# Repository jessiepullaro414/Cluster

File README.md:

# Cluster

**How to run everything: [RUNNING.md](RUNNING.md).**

Digital restomod instrument cluster for a 1966 Mustang: round displays in the stock round holes, custom reprinted faceplate, stock outer dash opening (457.2 x 116.69mm hard limit, 441.09 x 105.54mm inner).

The center gauge runs Linux with LIVI (CarPlay / Android Auto) or Android Automotive; the four small gauges are driven by a separate MCU board. The boards share a CAN bus with `ecu-pcb`.

## Boards

| Dir | Role | Core | Board |
|---|---|---|---|
| [brain/](brain/) | Centre-screen board, **the same in every car**: wireless Android Auto / CarPlay host with sound, two screen ports | Toradex Verdin iMX95 WB SoM (screwed down on M2 standoffs, heatsink-ready), screen port A (MIPI DSI) and B (LVDS, single or dual link), TAC5112-Q1 audio codec, two USB-C host ports | 127.5 x 95.3mm |
| [panel-tsd/](panel-tsd/) | Panel board for the TSD TST040HDBC-42 4 in 800-nit round MIPI panel: its FPC connector, +/-6 V bias, backlight, and the input from port A | TPS65131-Q1, TPS61165-Q1 | 75.4 x 52.3mm |
| [gauges/](gauges/) | 4 small aux gauges, resistive sender front end, Hall or two-wire VR speed, tach and six 12 V indicator-lamp inputs | NXP S32K144, 4x GC9A01 round SPI | 447.1 x 61.0mm |

**One brain board for every car (2026-10-20).** The centre-screen board no longer depends on the car or the panel. Everything that does moved off it: the panel's connector, bias supply, polarity jumpers and backlight are on a small board behind that panel, joined to the brain board by a ribbon on one of two screen ports (DSI for MIPI panels, LVDS for automotive and large panels; an RGB panel gets an LVDS-to-RGB receiver on its panel board). Each port has its own current-limited 5 V switch, panel control lines, an I2C bus and a panel-ID resistor the software reads. Pin tables and the rules for a new panel board: [docs/screen-ports.md](docs/screen-ports.md). A different car (a 1968 Mustang, a 1972 Alfa Romeo GTV) needs its own gauges board (generated from the same scripts with its own gauge positions), panel boards for its screens and a faceplate; the brain board stays the same. The 1966-only `display/` and the RGB variant `display-rgb/` are in `archive/`; the RGB panel's own panel board waits for that panel's datasheet. Not confirmed yet: that the Verdin iMX95 drives the DSI and LVDS screens independently at the same time (the i.MX 95 can; question 9 in `docs/rfq-drafts.md` section 2).

**Status: prototype, not yet ordered.** Fabrication readiness board by board: `docs/electrical-review.md` section 9.4 (panel-tsd/ should wait for TSD's connector answer); first power-up checklist: section 9.5. All three boards are six-layer and routed with 0 unconnected nets, and have generated BOMs (`brain/ClusterBrain_BOM.html`, `panel-tsd/ClusterPanelTSD_BOM.html`, `gauges/ClusterGauges_BOM.html`). brain/ and panel-tsd/ are ERC-clean (0 violations); gauges/ shows 4 known ERC items (a SWCLK pin, the MCU and buck supply pins flagged as undriven, and a `+5V` power-flag note). DRC: brain/ reports 4 `hole_clearance` errors (the USB-C receptacle J17's own land pattern: its GND pads sit 0.194 mm from its locating pegs against the 0.25 mm default, see `fab/README.md`) plus silkscreen and library-copy warnings; panel-tsd/ reports only `solder_mask_bridge` errors at the intentional open polarity jumpers JP1/JP2; gauges/ the same at its open CAN-termination jumpers JP1/JP2, plus warnings. Nothing has been fabricated, powered or firmware-tested. Mechanical fit is checked against a 3D assembly in a factory-style housing (`docs/dash-assembly.md`, no clashes), and gauges/ (447.1 mm) is wider than the 441.09 mm inner opening dimension, within the 457.2 mm outer limit. Installing in a car with the stock wiring (grounds, the ammeter wires, the dimmer, warning lamps, CAN termination): `docs/harness.md`.

**The owner's decisions, 2026-11-04** (`docs/electrical-review.md` 9.3): two-wire VR speed sensors are supported directly (J12, U13, simulated only so far); the ALT gauge is a voltmeter; an unsuppressed load dump may sacrifice the TVS and fuse; friction-lock harness headers stay as they are; a parked module whose wake timer cannot be set powers off rather than sleeps. The dash-light knob is read by a pulsed load on the board, so nothing goes under the dash (simulated only so far; the rheostat's 12 ohm full scale is an estimate until a real switch is measured).

**Product review for fabrication, 2026-11-03** (`docs/electrical-review.md` section 9): both 12 V input stages rewired to TI's LM74930 topology (the sense resistor had been on the input side, which broke the short-circuit protection, put 12 V across a +-0.3 V pin pair at every power-up and let a reversed battery reach pins rated -1 V), with an inrush (dV/dt) network, a bidirectional TVS so a reversed battery is simply blocked, and Kelvin sense taps built into the resistor's land pattern (the router's copper had been pulling the gauges breaker from 1.49 A down to about 0.45 A). brain/ gained an ignition power latch: the key starts the module from any state and software can switch the board fully off with the car parked. gauges/ measures each sender with its excitation on and off, cancelling the engine-to-dash ground offset that made a hot engine or a full tank read as a shorted sender; the sender excitation and the 12 V pull-up rail (now also the Hall sender's supply on J9 pin 3) switch off with the car off; the car-CAN terminator is switched in with solder jumpers. Open decisions are in section 9.3.

**Product review, 2026-10-18** (`docs/electrical-review.md` section 8a): the Verdin module now has Toradex's four M2 standoffs (S1/S2 hold-down, S3/S4 for the Verdin Industrial Heatsink) and a keepout that follows the real module outline; the LM74930 FETs on both boards are Vishay SQJ460AEP (PowerPAK SO-8L) instead of the NRND SOT-23 PMV55ENEA; the gauges buck has the datasheet's 2.2 uH / 16 V output parts; the line-out ESD array is bidirectional; the panel-bias outputs use 16 V capacitors; the inner small gauges moved to the measured +/-118 mm. Still open before ordering: the TSD panel's pinout and connector (`docs/rfq-drafts.md` section 1), the Verdin module's availability and heatsink (section 2), the depth stack-up (`docs/mechanical-stackup.md`), the backlight driver's temperature (D-04), the small displays' -20 to +70 C rating (G-15, section 6), and licensing.

## How the boards talk

gauges/ is the gateway. It is the only board that touches the car CAN bus (CAN0, receive-only in firmware) and it forwards filtered values to brain/ over a private two-node CAN link (gauges/ CAN1 to brain/ CAN). Android therefore cannot transmit on the vehicle bus. The protocol (`protocol/can_protocol.py`, revision 2) generates the DBC, a spec and a C header; the private link carries a rolling counter and CRC-8, and the car-bus side has a selectable Haltech V2 profile. Speed comes from a Hall-effect sender on gauges/ (for cable-driven cars) or from the ECU over CAN. gauges/ also reads six 12 V-active indicator lamps (left/right turn, high beam, brake, alternator, oil; each has a DNP pull-up for a ground-switched lamp). The two turn-signal arrows on the dash are physical: green LEDs (ROHM CSL0902ET1C) on gauges/, each lit straight from its turn-signal wire through a 1.8 k resistor so they flash like the old bulbs even with the software off (their X positions are placeholders until the faceplate drawing exists) and a tach input (ECU or coil-driver output; coil-negative on a points ignition is not validated), sent to brain/ in the `Indicators` message (which also carries the dimmer level) and the `Rpm` signal. brain/ has a rotary-dial input (J11), an ignition wake circuit, an audio path (balanced stereo line-out J14 and a microphone J15 on a TI TAC5112-Q1 codec), a USB-C host port (J17, 1.5 A, for a phone or a wireless-projection dongle), a DNP 1x6 header (J16) for an Apple MFi coprocessor daughterboard, with I2C, reset and a GPIO-switched 5 V supply and bench headers for the A55 console UART (J12), USB (J13), JTAG (J8) and buttons (J9).

## Known limits of the layouts

- **Six layers, two solid GND planes (2026-10-19).** Stack-up JLC06161H-3313: F.Cu signal, In1 GND, In2 signal, In3 signal plus the +5V (brain/, panel-tsd/) or +3V3 (gauges/) pour, In4 GND, B.Cu signal. Every net except GND gets a net-class layer restriction in the router input (`use_layer F.Cu In2.Cu In3.Cu B.Cu`; FreeRouting ignores a layer_rule "active off"), so In1 and In4 carry no track at all, only the GND fill and vias, and `review/layout_checks.py` fails a board if any other net lands there. Every outer-layer signal has a GND plane 0.0994 mm below it. In2 and In3 sit 0.55 mm from their planes and only 0.11 mm from each other, so a signal on one can couple broadside into the other. On brain/ the USB-C phone pair (USB2_DP/DN, about 30 mm) runs about 25 mm on In3, both legs together. PG_5V, the buck's own power-good pin, runs on F.Cu 0.24 mm from its switch copper beside U2 (`layout_checks.py`). On panel-tsd/ the backlight PWM line crosses the backlight's switch node in plan view on In3, with the In1 plane between them. Until 2026-10-19 both boards were four-layer with signals routed through the GND and supply pours (about 1.5 m on the old display/, 9 m on gauges/). gauges/ routes VIN_PROT, VIN_FUSED and +5V at 0.4 mm from the start, and every power net on it now passes `layout_checks.py`'s 20 K current check. Details: `docs/electrical-review.md` section 8b.
- **Battery-path and port copper on brain/ (2026-10-20, from display/).** VBAT_IN, VBAT_F, SENSE_OUT, COMMON and +12V_PROT (up to 2.6 A behind the 5 A fuse) now route on the 1 oz outer layers only, at 0.3 mm with 1.0/0.5 mm vias, and after widening each gets an F.Cu pour in a 2 mm band around its own copper (`route_board.py`, `BATTERY_PATH_NETS` and `add_battery_pours()`). No battery copper is on In2/In3 any more (until now about 60 mm of VBAT_F was, which IPC-2221 rates at about 1.3 A). `review/layout_checks.py` now rates each of these nets along the path the current takes (J2 -> F1 -> R1 -> Q2 -> Q1 -> the buck's VIN pins), counting the pour beside a track and the vias, and lists branch copper to milliamp pins (LM74930 sense pins, small caps) separately. R2 and C3 sit on R1's input side (`brain/cells.py`), so nothing lies between R1 and Q2. Each screen port's switched 5 V (PORTA_5V, PORTB_5V, up to the switch's 1.98 A) gets the same outer-layer route and pour. VBAT_IN, VBAT_F, SENSE_OUT and PORTA_5V pass; what is left are short necks where the path meets a pin: COMMON 2.1 mm at down to 0.34 mm at the FETs' source pins, +12V_PROT 1.0 mm at down to 0.56 mm at the buck's 0.4 mm VIN pins, PORTB_5V 0.7 mm at 0.45 mm, each a few mW at full current. Still worth a thermal-camera look at 2.5 A on the first board. Details: `docs/electrical-review.md` section 8b.
- **brain/ shrunk (2026-11-06).** 184.8 x 104.9 mm to 127.5 x 95.3 mm, 37 % less area, parts' courtyards from 33 % to 52 % of the board. The battery path and the screen ports' 5 V are planned copper now as well, worst 15 K by IPC-2221, and J2 sits on the right edge with its wire mouth facing out: it used to face the Verdin module. Each USB-C pair has a common-mode choke. `docs/electrical-review.md` section 9.5c. gauges/ J1 had the same mouth fault: see below.
- **gauges/ J1 (2026-11-06).** Its wire mouth looked down the board at C59. It's turned round now and sits at the top edge, with the fuse beside pin 1 and the input TVS beside the fuse, and the board is 61.0 mm tall, from 65.9. The screen connectors didn't move. J1's wires are in the housing's clash check with 0.5 mm to spare, on assumed wire and bend sizes, and no way out of the housing is drawn for them yet. Calculated, not measured. `docs/electrical-review.md` section 9.5d.
- **5 V copper on brain/ (2026-11-06).** Until now all of the buck's output left L1 on one 0.2 mm track: 1021 K by IPC-2221 at the Alfa's 5.7 A, 284 mV down at J1, and `layout_checks.py` passed it as "pour-carried?". `brain/power_route.py` now plans the copper that carries current, with vias into the In3 pour at L1, J1 and each port switch, and `review/power_sheet.py` solves the net with its pours as copper sheets for both cars: worst track 2.7 K, worst via 4.3 K, 13 mV. It gates each route and the fab package. Calculated, not measured. The same re-route left no under-width copper on the battery path or the ports, so the necks listed above are gone. Details: `docs/electrical-review.md` section 9.5b.
- **Screen-port pairs.** On brain/ every DSI and LVDS pair runs from the Verdin socket straight to its port connector on F.Cu over the In1 plane, planned by `brain/fan_route.py` (no length difference inside a pair; DSI about 5.4 mm, LVDS about 35 mm, under the module), with GND guard tracks between pairs where the socket has a ground pin. On panel-tsd/ the three DSI lanes and the clock are autorouted on F.Cu and B.Cu only (each leg is about 52 ohm on its own, so a pair stays near 100 ohm even where the router separates its legs); the router's skew inside a pair is up to 5.5 mm (about 37 ps, 2 % of a bit at 500 Mbit/s). The 0.16 mm geometry is field-solved by `review/dsi_impedance.py` (96.4 to 103.1 ohm differential on JLC06161H-3313); that is a 2-D solve on the board house's nominal stack-up, not a measurement: order with controlled impedance and a coupon (`fab/README.md`).
- The panel connector, the panel bias-pin polarity (open jumpers JP1/JP2; a diode-test check before bridging is in `fab/README.md`) and the wake-pin polarity are unconfirmed. The panel bias rails are set to +5.98 V and -6.05 V, inside the ICNL9707 driver's 4.5 to 6.5 V operating range with margin to its 6.6 V absolute maximum (the panel sheet's 6.5 V is at the top of that range; question 8 in `docs/rfq-drafts.md`).

Open items and rationale live in the working plan, not here. Panel: TSD TST040HDBC-42 (4in round, 800 nits, -30..+80C, 101.52 mm active circle: fits the 105.54 mm dash opening height, but NOT a stock 89.26 mm speedometer hole without cropping, see `docs/mechanical-fit.md`). Harness connectors are decided for both boards (`docs/harness.md`, 2026-10-17). Known TBDs: the panel's unresolved bias-pin polarity (open solder jumpers JP1/JP2), measured sender curves (`docs/sender-calibration.md`: the dash shows the raw sender resistance for this), and everything that needs real hardware. The gauges firmware's key-off sleep (S32K144 VLPS, woken by the ignition line) is written and host-tested, not run on a board.

## Wireless Android Auto / CarPlay hardware (2026-10-16)

Required by the owner. brain/ carries the physical pieces: audio codec and connectors, two USB-C host ports, the Verdin WB module's Wi-Fi 6 / Bluetooth 5.4 (antennas are a mechanical item) and a reserved DNP MFi access point. **Licensing (Apple MFi for CarPlay, Google's Android Auto receiver terms) is a separate business gate (plan item B5) that hardware does not solve.** Wiring, antenna rules, software bring-up and what is unverified: [docs/audio-and-usb.md](docs/audio-and-usb.md).

## Workflow

Everything is generated from scripts. Never hand-edit the KiCad files; change the script and regenerate. In `brain/`, `panel-tsd/` or `gauges/`:

```
python build_schematic.py   # schematic + ERC self-checks
python build_pcb.py         # placement + DRC-style self-checks
python route_board.py       # FreeRouting (brain/ also adds the planned screen-port pairs), verified against real kicad-cli DRC
python ../review/layout_checks.py <dir>   # GND planes clean, switch-node spacing, fast-net layers, power-path current
python ../run_drc.py <Board>.kicad_pcb
python build_bom.py         # BOM with coverage/value-spelling checks
```

`route_board.py` needs `tools/freerouting-2.2.4.jar` (gitignored, ~57MB; download from the FreeRouting releases) and a JRE.

## Archive

[archive/](archive/) holds superseded work kept for reference only, not maintained:

- `display-1966/`: the 1966 Mustang's one-panel Verdin carrier (2026-09-25 to 2026-10-20), replaced by brain/ + panel-tsd/; its fab package is in `display-1966/fab/`.
- `display-rgb/`: display/ with an LVDS-to-RGB receiver for the Anders 4.2 in RGB panel, routed; the receiver becomes that panel's panel board once its datasheet arrives.
- `single-board-s32k144-bt817aq/`: the original one-board design (S32K144 + BT817AQ + round ST7701S speedo + 4 GC9A01), fully routed 252/252 before the Android pivot.
- `.../sense-abandoned-bar-panel-attempt/`: an unfinished CAN-only sensor board from the abandoned wide bar-panel direction.

Scripts there use their old relative paths (`tools/`, `run_drc.py`) and will need adjusting to run.

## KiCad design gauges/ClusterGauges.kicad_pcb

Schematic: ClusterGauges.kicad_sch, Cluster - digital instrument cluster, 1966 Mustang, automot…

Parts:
C1: 10uF 50V X7R CIN (AEC-Q200); C_1210_3225Metric
C2, C45: 22uF 16V X7R COUT (AEC-Q200); C_1210_3225Metric
C3: 1uF X7R (AEC-Q200); C_0603_1608Metric
C4, C5: 18pF (AEC-Q200); C_0603_1608Metric
C6, C7: 100nF (AEC-Q200); C_0603_1608Metric
C8: 1uF (AEC-Q200); C_0603_1608Metric
C11: 100nF BOOT cap (AEC-Q200); C_0603_1608Metric
C12: 1uF VCC decouple (AEC-Q200); C_0603_1608Metric
C13, C40: 100nF VCC decouple (AEC-Q200); C_0603_1608Metric
C14, C41: 100nF VIO decouple (AEC-Q200); C_0603_1608Metric
C15: 100nF VBAT decouple (AEC-Q200); C_0603_1608Metric
C16, C42: 4.7nF SPLIT stabilization (AEC-Q200); C_0603_1608Metric
C17, C18, C19, C20: 100nF VCI decouple (AEC-Q200); C_0603_1608Metric
C28: 100nF ADC_FUEL smoothing (AEC-Q200); C_0603_1608Metric
C29: 100nF ADC_OIL smoothing (AEC-Q200); C_0603_1608Metric
C30: 100nF ADC_TEMP smoothing (AEC-Q200); C_0603_1608Metric
C31: 100nF ADC_BATT smoothing (AEC-Q200); C_0603_1608Metric
C43: 1nF input filter (AEC-Q200); C_0603_1608Metric
C44: 10nF input filter (AEC-Q200); C_0603_1608Metric
C46: 220nF 50V CHF at VIN (AEC-Q200); C_0603_1608Metric
C47: 1uF CVS (50V); C_0805_2012Metric
C48: 100nF CCAP (50V); C_0603_1608Metric
C49: 100nF CTMR; C_0603_1608Metric
C50: 10nF input filter, Left turn (AEC-Q200); C_0603_1608Metric
C51: 10nF input filter, Right turn (AEC-Q200); C_0603_1608Metric
C52: 10nF input filter, High beam (AEC-Q200); C_0603_1608Metric
C53: 10nF input filter, Brake / parking brake (AEC-Q20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; C_0603_1608Metric
C54: 10nF input filter, Alternator / charge (AEC-Q200); C_0603_1608Metric
C55: 10nF input filter, Oil pressure (AEC-Q200); C_0603_1608Metric
C56: 10nF input filter, tach (AEC-Q200); C_0603_1608Metric
C57: 220nF input filter, dash dimmer (AEC-Q200); C_0603_1608Metric
C58: 1uF X7R LDO input (AEC-Q200); C_0603_1608Metric
C59, C60: 10uF 50V X7S extra bulk at VIN_PROT (AEC-Q200); C_1210_3225Metric
C61: 4.7nF 50V CdVdT, HGATE inrush limit (AEC-Q200); C_0603_1608Metric
C62: 100nF 50V CIN at the fused input (AEC-Q200); C_0603_1608Metric
C63: 100nF 50V U12 VS decoupling (AEC-Q200); C_0603_1608Metric
C64: 10nF 50V VPULL output (ESD, AEC-Q200); C_0603_1608Metric
C65: 1uF X7R U11 input (AEC-Q200); C_0603_1608Metric
C66: 100nF SENDER_EXC (AEC-Q200); C_0603_1608Metric
C67: 100nF SENDER_BIAS (AEC-Q200); C_0603_1608Metric
C68: 4.7nF VR filter, wire A (AEC-Q200); C_0603_1608Metric
C69: 4.7nF VR filter, wire B (AEC-Q200); C_0603_1608Metric
C70: 100nF U13 supply (AEC-Q200); C_0603_1608Metric
D1: SMCJ33CA bidirectional automotive TVS (AEC-Q101) 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; D_SMC
D10, D11: BAV99-Q input clamp (AEC-Q101); SOT-23
D12: BAV99-Q fuel input clamp (AEC-Q101); SOT-23
D13: BAV99-Q oil input clamp (AEC-Q101); SOT-23
D14: BAV99-Q temp input clamp (AEC-Q101); SOT-23
D15: BAV99-Q battery divider clamp (AEC-Q101); SOT-23
D16: BAV99-Q input clamp, Left turn (AEC-Q101); SOT-23
D17: BAV99-Q input clamp, Right turn (AEC-Q101); SOT-23
D18: BAV99-Q input clamp, High beam (AEC-Q101); SOT-23
D19: BAV99-Q input clamp, Brake / parking brake (AEC-Q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; SOT-23
D20: BAV99-Q input clamp, Alternator / charge (AEC-Q10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; SOT-23
D21: BAV99-Q input clamp, Oil pressure (AEC-Q101); SOT-23
D22: BAV99-Q input clamp, tach (AEC-Q101); SOT-23
D23: BAV99-Q input clamp, dash dimmer (AEC-Q101); SOT-23
D24: BAV99-Q reverse clamp, Left turn arrow LED (AEC-Q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; SOT-23
D25: BAV99-Q reverse clamp, Right turn arrow LED (AEC-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; SOT-23
D26: CSL0902ET1C green LED, Left turn arrow; CSL0902_1608
D27: CSL0902ET1C green LED, Right turn arrow; CSL0902_1608
D28: SM24CANB-02HTG TVS on the car CAN bus, at J7 (AEC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; SOT-23
D29: SM24CANB-02HTG TVS on the fuel and oil sender wir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; SOT-23
D30: SM24CANB-02HTG TVS on the coolant sender wire, at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; SOT-23
D31: SM24CANB-02HTG TVS on the private CAN link, at J8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; SOT-23
D32: SM24CANB-02HTG TVS on the Hall speed wire, at J9 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; SOT-23
D33: SZMMSZ3V6T1G 3.6V zener clamp on +3V3, absorbs a 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; D_SOD-123
D34: BAV99-Q LM74930 VS supply diode, blocks a reverse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; SOT-23
D35: BAV99-Q input clamp, VR wire A (AEC-Q101); SOT-23
D36: BAV99-Q input clamp, VR wire B (AEC-Q101); SOT-23
D37: BAV99-Q both sections in series, blocks a negativ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; SOT-23
F1: Mini blade holder, 2A Littelfuse 297 fuse (SAE J2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; Fuseholder_Blade_Mini_Keystone_3568
J1: Phoenix MKDS 1,5/3-5,08: 12V, GND, ignition (20 A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; TerminalBlock_Phoenix_MKDS-1,5-3-5.08_1x03_P5.08mm_Horizont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
J2: SWD Tag-Connect TC2030-IDC-NL (pin order per Tag-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; Tag-Connect_TC2030-IDC-NL_2x03_P1.27mm_Vertical
J7: KK-254 22-27-2051: CAN0 + 3 sender inputs (22 AWG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; Molex_KK-254_AE-6410-05A_1x05_P2.54mm_Vertical
J8: KK-254 22-27-2031, private CAN link to display/ J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; Molex_KK-254_AE-6410-03A_1x03_P2.54mm_Vertical
J9: KK-254 22-27-2031, Hall speed sender (signal, gro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; Molex_KK-254_AE-6410-03A_1x03_P2.54mm_Vertical
J10: KK-254 22-27-2081, indicator lamp inputs (6 x 12 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; Molex_KK-254_AE-6410-08A_1x08_P2.54mm_Vertical
J11: KK-254 22-27-2021, tach input (signal + ground; 2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; Molex_KK-254_AE-6410-02A_1x02_P2.54mm_Vertical
J12: KK-254 22-27-2021, two-wire VR speed sensor (22 A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; Molex_KK-254_AE-6410-02A_1x02_P2.54mm_Vertical
JP1: Solder jumper: bridge with JP2 to terminate the c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; SolderJumper-2_P1.3mm_Open_RoundedPad1.0x1.5mm
JP2: Solder jumper: bridge with JP1 to terminate the c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; SolderJumper-2_P1.3mm_Open_RoundedPad1.0x1.5mm
L1: 2.2uH power XAL5030-222ME (AEC-Q200); L_Coilcraft_XAL5030-XXX
L2: ferrite bead (AEC-Q200); L_0603_1608Metric
Q1: SQJ460AEP ideal diode (DGATE); PowerPAK_SO-8L_Single
Q2: PMV37ENEA automotive (AEC-Q101) - shared aux-gaug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; SOT-23
Q3: SQJ460AEP pass (HGATE); PowerPAK_SO-8L_Single
Q4: MMBT5551Q dimmer test load switch (AEC-Q101); SOT-23
R1: 10k pull-up (AEC-Q200); R_0603_1608Metric
R2: 10k (AEC-Q200); R_0603_1608Metric
R3: 2.49k (AEC-Q200); R_0603_1608Metric
R4, R5: 60R split termination (AEC-Q200), switched in by 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; R_0603_1608Metric
R6, R7, R8, R9: 120R VLED series (self-calculated for ~15mA at 5V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; R_0603_1608Metric
R10: 100R BL_EN gate resistor (AEC-Q200); R_0603_1608Metric
R11: 10k LPSPI2_SIN pull-down, idle-state definition (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; R_0603_1608Metric
R16: 1k fuel pull-up to SENDER_EXC, 1206: a wire short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; R_1206_3216Metric
R17: 1k oil pull-up to SENDER_EXC, 1206 (AEC-Q200); R_1206_3216Metric
R18: 1k coolant temp pull-up to SENDER_EXC, 1206 (AEC-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; R_1206_3216Metric
R19: 49.9k battery divider top, self-calculated for 9-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; R_0603_1608Metric
R20: 10k battery divider bottom, self-calculated for 9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; R_0603_1608Metric
R40: 10k STB pulldown, normal mode while MCU resets (A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; R_0603_1608Metric
R41, R42: 60R split termination (AEC-Q200); R_0603_1608Metric
R43: 4.7k pull-up to VPULL for open-collector senders 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; R_0603_1608Metric
R44: 33k series (AEC-Q200); R_0603_1608Metric
R45: 15k divider bottom (AEC-Q200); R_0603_1608Metric
R46: 56k series (AEC-Q200); R_0603_1608Metric
R47: 27k divider bottom (AEC-Q200); R_0603_1608Metric
R48: 49.9R 1% RSET; R_0603_1608Metric
R49: 5m 1% sense (Susumu KRL3216E-M-R005-F-T5); R_1206_3216Metric_Kelvin
R50: 80.6k 1% RILIM (1.5A breaker); R_0603_1608Metric
R51: 100k OV top; R_0603_1608Metric
R52: 2.05k OV bot (clamp 29.9V); R_0603_1608Metric
R53: 100k UV top; R_0603_1608Metric
R54: 11.5k UV bot (cut-off 5.5V); R_0603_1608Metric
R55: 1k fuel ADC series (AEC-Q200); R_0603_1608Metric
R56: 1k oil ADC series (AEC-Q200); R_0603_1608Metric
R57: 1k temp ADC series (AEC-Q200); R_0603_1608Metric
R58: 33k series, Left turn (AEC-Q200); R_0603_1608Metric
R59: 15k divider bottom, Left turn (AEC-Q200); R_0603_1608Metric
R60: 4.7k pull-up to VPULL, DNP: fit only if the Left 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; R_0603_1608Metric
R61: 33k series, Right turn (AEC-Q200); R_0603_1608Metric
R62: 15k divider bottom, Right turn (AEC-Q200); R_0603_1608Metric
R63: 4.7k pull-up to VPULL, DNP: fit only if the Right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; R_0603_1608Metric
R64: 33k series, High beam (AEC-Q200); R_0603_1608Metric
R65: 15k divider bottom, High beam (AEC-Q200); R_0603_1608Metric
R66: 4.7k pull-up to VPULL, DNP: fit only if the High 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; R_0603_1608Metric
R67: 33k series, Brake / parking brake (AEC-Q200); R_0603_1608Metric
R68: 15k divider bottom, Brake / parking brake (AEC-Q2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; R_0603_1608Metric
R69: 4.7k pull-up to VPULL, DNP: fit only if the Brake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; R_0603_1608Metric
R70: 33k series, Alternator / charge (AEC-Q200); R_0603_1608Metric
R71: 15k divider bottom, Alternator / charge (AEC-Q200); R_0603_1608Metric
R72: 4.7k pull-up to VPULL, DNP: fit only if the Alter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; R_0603_1608Metric
R73: 33k series, Oil pressure (AEC-Q200); R_0603_1608Metric
R74: 15k divider bottom, Oil pressure (AEC-Q200); R_0603_1608Metric
R75: 4.7k pull-up to VPULL, DNP: fit only if the Oil p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; R_0603_1608Metric
R76, R77: 18k series, tach, 200V (AEC-Q200); R_1206_3216Metric
R78: 15k divider bottom, tach (AEC-Q200); R_0603_1608Metric
R79: 4.7k pull-up to VPULL, DNP: fit only for an open-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; R_0603_1608Metric
R80: 22k divider top, dash dimmer (AEC-Q200); R_0603_1608Metric
R81: 4.7k divider bottom, dash dimmer (AEC-Q200); R_0603_1608Metric
R82: 1.8k LED series, Left turn arrow (AEC-Q200); R_1206_3216Metric
R83: 1.8k LED series, Right turn arrow (AEC-Q200); R_1206_3216Metric
R84: 33R SPI SCK series termination at the MCU (AEC-Q2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; R_0603_1608Metric
R85: 33R SPI MOSI series termination at the MCU (AEC-Q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; R_0603_1608Metric
R86: 100k BL_GATE pull-down, backlights stay off until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; R_0603_1608Metric
R87: 100k CAN0_EN pull-down, defined state while the M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; R_0603_1608Metric
R88: 100k CAN0_STB_N pull-down, defined state while th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; R_0603_1608Metric
R89: 100R RG, HGATE to the dV/dt capacitor (AEC-Q200); R_0603_1608Metric
R90: 10k VPULL_EN series (TI R(SER)) (AEC-Q200); R_0603_1608Metric
R91: 3.24k 1% R(CL), 148 mA current limit (AEC-Q200); R_0603_1608Metric
R92: 100k DELAY pull-up to VS: auto-retry (AEC-Q200); R_0603_1608Metric
R94: 100k SENDER_EXC_EN pull-down, excitation off whil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; R_0603_1608Metric
R95: 6.8k ADC bias, fuel sender (AEC-Q200); R_0603_1608Metric
R96: 6.8k ADC bias, oil sender (AEC-Q200); R_0603_1608Metric
R97: 6.8k ADC bias, coolant sender (AEC-Q200); R_0603_1608Metric
R98: 100k SENDER_BIAS pull-down while the MCU resets (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; R_0603_1608Metric
R99: 47k series, VR wire A, 200V (AEC-Q200); R_1206_3216Metric
R100: 47k series, VR wire B, 200V (AEC-Q200); R_1206_3216Metric
R101: 10k from the VR filter to U13 IN+ (AEC-Q200); R_0603_1608Metric
R102: 680k hysteresis, U13 output to IN+ (AEC-Q200); R_0603_1608Metric
R103: 2M bias of U13 IN- to +3V3 (AEC-Q200); R_0603_1608Metric
R104: 2M bias of U13 IN- to GND (AEC-Q200); R_0603_1608Metric
R105: 330R dimmer test load, 1W (AEC-Q200); R_2512_6332Metric
R106: 1k base resistor, dimmer test load (AEC-Q200); R_0603_1608Metric
R107: 47k base pull-down, dimmer test load (AEC-Q200); R_0603_1608Metric
U1: NXP S32K144 automotive (AEC-Q100); LQFP-64_10x10mm_P0.5mm
U2: LMR33630-Q1 (AEC-Q100 G1); TI_RNX0012C_VQFN-HR-12_2x3mm_P0.5mm
U3: LM74930-Q1 (AEC-Q100 G1); Texas_RGE0024H_VQFN-24-1EP_4x4mm_P0.5mm_EP2.7x2.7mm
U4: TLV733P-Q1 (AEC-Q100 G1); SOT-23-5
U5: NXP TJA1043T automotive CAN transceiver (AEC-Q100); SOIC-14_3.9x8.7mm_P1.27mm
U6: Raystar RFA401280B-AYW-DNF1 - Fuel level gauge; Amphenol_F32Q-1A7x1-11018_1x18-1MP_P0.5mm_Horizontal
U7: Raystar RFA401280B-AYW-DNF1 - Oil pressure gauge; Amphenol_F32Q-1A7x1-11018_1x18-1MP_P0.5mm_Horizontal
U8: Raystar RFA401280B-AYW-DNF1 - Coolant temp gauge; Amphenol_F32Q-1A7x1-11018_1x18-1MP_P0.5mm_Horizontal
U9: Raystar RFA401280B-AYW-DNF1 - Battery voltage gau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; Amphenol_F32Q-1A7x1-11018_1x18-1MP_P0.5mm_Horizontal
U10: TCAN1044V-Q1 (AEC-Q100 G1); SOIC-8_3.9x4.9mm_P1.27mm
U11: TPS22918-Q1 sender excitation switch (AEC-Q100 G2); SOT-23-6
U12: TPS1H000-Q1 switched 12 V for pull-ups and the Ha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; TI_DGN0008K_HVSSOP-8-1EP_3x3mm_P0.65mm_EP1.57x1.89mm
U13: TLV7031-Q1 VR speed comparator (AEC-Q100 G1); SOT-23-5
Y1: 8MHz (AEC-Q200); Crystal_SMD_3225-4Pin_3.2x2.5mm

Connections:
+3V3: C3.1, C6.1, C7.1, C14.1, C17.1, C18.1, C19.1, C20.1, C41.1, C65.1, C70.1, D10.2 (K2), D11.2 (K2), D12.2 (K2), D13.2 (K2), D14.2 (K2), D15.2 (K2), D16.2 (K2), D17.2 (K2), D18.2 (K2), D19.2 (K2), D20.2 (K2), D21.2 (K2), D22.2 (K2), D23.2 (K2), D33.1 (K), D35.2 (K2), D36.2 (K2), J2.1 (VCC), L2.1, R1.1, R103.1, U1.7 (VDD), U1.41 (VDD), U4.5 (OUT), U5.5 (VIO), U6.16 (VCI3V3), U7.16 (VCI3V3), U8.16 (VCI3V3), U9.16 (VCI3V3), U10.5 (VIO), U11.1 (VIN), U13.5 (VCC)
+5V: C2.1, C13.1, C40.1, C45.1, C58.1, L1.2, R2.1, R6.1, R7.1, R8.1, R9.1, U4.1 (IN), U4.3 (EN), U5.3 (VCC), U10.3 (VCC)
ADC_BATT: C31.1, D15.3 (CA), R19.2, R20.1, U1.47 (ADC_BATT)
ADC_FUEL: C28.1, D12.3 (CA), R55.2, R95.2, U1.50 (ADC_FUEL)
ADC_OIL: C29.1, D13.3 (CA), R56.2, R96.2, U1.49 (ADC_OIL)
ADC_TEMP: C30.1, D14.3 (CA), R57.2, R97.2, U1.48 (ADC_TEMP)
AUX_CS0: U1.13 (AUX_CS0), U6.10 (CS)
AUX_CS1: U1.14 (AUX_CS1), U7.10 (CS)
AUX_CS2: U1.15 (AUX_CS2), U8.10 (CS)
AUX_CS3: U1.16 (AUX_CS3), U9.10 (CS)
AUX_DC0: U1.17 (AUX_DC0), U6.13 (RS)
AUX_DC1: U1.22 (AUX_DC1), U7.13 (RS)
AUX_DC2: U1.23 (AUX_DC2), U8.13 (RS)
AUX_DC3: U1.24 (AUX_DC3), U9.13 (RS)
AUX_RST: U1.42 (AUX_RST), U6.15 (RESET), U7.15 (RESET), U8.15 (RESET), U9.15 (RESET)
AUX_VLED_RTN: Q2.3 (D), U6.8 (VLED-), U7.8 (VLED-), U8.8 (VLED-), U9.8 (VLED-)
BL_EN: R10.1, U1.39 (BL_EN)
BL_GATE: Q2.1 (G), R10.2, R86.1
BOOT_CAP: C11.1, U2.4 (BOOT)
CAN0_EN: R87.1, U1.18 (CAN0_EN), U5.6 (EN)
CAN0_H: D28.1 (IO1), J7.1 (CAN0_H), JP1.1 (A), U5.13 (CANH)
CAN0_L: D28.2 (IO2), J7.2 (CAN0_L), JP2.2 (B), U5.12 (CANL)
CAN0_RX: U1.6 (CAN0_RX), U5.4 (RXD)
CAN0_SPLIT: C16.1, R4.2, R5.1, U5.11 (SPLIT)
CAN0_STB_N: R88.1, U1.19 (CAN0_STB_N), U5.14 (STB_N)
CAN0_TERM_H: JP1.2 (B), R4.1
CAN0_TERM_L: JP2.1 (A), R5.2
CAN0_TX: U1.5 (CAN0_TX), U5.1 (TXD)
CAN1_H: D31.1 (IO1), J8.1 (CAN1_H), R41.1, U10.7 (CANH)
CAN1_L: D31.2 (IO2), J8.2 (CAN1_L), R42.2, U10.6 (CANL)
CAN1_RX: U1.52 (CAN1_RX), U10.4 (RXD)
CAN1_SPLIT: C42.1, R41.2, R42.1
CAN1_STB: R40.1, U1.60 (CAN1_STB), U10.8 (STB)
CAN1_TX: U1.51 (CAN1_TX), U10.1 (TXD)
CAP_CP: C48.1, U3.23 (CAP)
COMMON: Q1.1 (S), Q1.2 (S), Q1.3 (S), Q3.1 (S), Q3.2 (S), Q3.3 (S), U3.2 (A), U3.15 (OUT)
CS_MINUS: R49.4 (S2), U3.19 (CS-)
CS_PLUS: R48.2, U3.20 (CS+)
DGATE: Q1.4 (G), U3.1 (DGATE)
DIM_ADC: C57.1, D23.3 (CA), R80.2, R81.1, U1.31 (DIM_ADC)
DIM_LOAD: D37.2 (K2), R105.1
DIM_LOAD_B: Q4.1 (B), R106.2, R107.1
DIM_LOAD_C: Q4.3 (C), R105.2
DIM_LOAD_EN: R106.1, U1.32 (DIM_LOAD_EN)
DIM_RAW: D37.1 (A1), J10.8 (DIM_RAW), R80.1
FB: R2.2, R3.1, U2.7 (FB)
HGATE: Q3.4 (G), R89.1, U3.14 (HGATE)
HGATE_DVDT: C61.1, R89.2
IGN_SENSE: C44.1, D11.3 (CA), R46.2, R47.1, U1.59 (IGN_SENSE)
ILIM: R50.1, U3.11 (ILIM)
LAMP_ALT: C54.1, D20.3 (CA), R70.2, R71.1, U1.43 (LAMP_ALT)
LAMP_ALT_RAW: J10.5 (LAMP_ALT), R70.1, R72.2
LAMP_BRAKE: C53.1, D19.3 (CA), R67.2, R68.1, U1.38 (LAMP_BRAKE)
LAMP_BRAKE_RAW: J10.4 (LAMP_BRAKE), R67.1, R69.2
LAMP_HIGH_BEAM: C52.1, D18.3 (CA), R64.2, R65.1, U1.37 (LAMP_HIGH_BEAM)
LAMP_HIGH_BEAM_RAW: J10.3 (LAMP_HIGH_BEAM), R64.1, R66.2
LAMP_OIL: C55.1, D21.3 (CA), R73.2, R74.1, U1.44 (LAMP_OIL)
LAMP_OIL_RAW: J10.6 (LAMP_OIL), R73.1, R75.2
LAMP_TURN_L: C50.1, D16.3 (CA), R58.2, R59.1, U1.35 (LAMP_TURN_L)
LAMP_TURN_L_RAW: J10.1 (LAMP_TURN_L), R58.1, R60.2, R82.1
LAMP_TURN_R: C51.1, D17.3 (CA), R61.2, R62.1, U1.36 (LAMP_TURN_R)
LAMP_TURN_R_RAW: J10.2 (LAMP_TURN_R), R61.1, R63.2, R83.1
LM_VS: C47.1, C48.2, D34.3 (CA), U3.6 (EN), U3.7 (MODE), U3.22 (VS)
LPSPI2_SCK: R84.2, U6.11 (SCL), U7.11 (SCL), U8.11 (SCL), U9.11 (SCL)
LPSPI2_SCK_MCU: R84.1, U1.29 (LPSPI2_SCK)
LPSPI2_SIN: R11.1, U1.26 (LPSPI2_SIN)
LPSPI2_SOUT: R85.2, U6.12 (SDA), U7.12 (SDA), U8.12 (SDA), U9.12 (SDA)
LPSPI2_SOUT_MCU: R85.1, U1.25 (LPSPI2_SOUT)
OSC_IN: C4.1, U1.11 (OSC_IN), Y1.1 (XTAL1)
OSC_OUT: C5.1, U1.12 (OSC_OUT), Y1.3 (XTAL2)
OV_DIV: R51.2, R52.1, U3.5 (OV), U3.16 (OVCLAMP)
RESET: J2.3 (nRESET), R1.2, U1.63 (RESET)
SENDER_BIAS: C67.1, R95.1, R96.1, R97.1, R98.1, U1.53 (SENDER_BIAS)
SENDER_EXC: C66.1, R16.1, R17.1, R18.1, U11.6 (VOUT)
SENDER_EXC_EN: R94.1, U1.46 (SENDER_EXC_EN), U11.3 (ON)
SENDER_FUEL: D29.1 (IO1), J7.3 (FUEL_SENSE), R16.2, R55.1
SENDER_OIL: D29.2 (IO2), J7.4 (OIL_SENSE), R17.2, R56.1
SENDER_TEMP: D30.1 (IO1), J7.5 (TEMP_SENSE), R18.2, R57.1
SENSE_HI: Q1.5 (D), R49.1, U3.24 (C)
SENSE_TAP: R48.1, R49.3 (S1), U3.18 (ISCP)
SPEED_IN: C43.1, D10.3 (CA), R44.2, R45.1, U1.58 (SPEED_IN)
SPEED_RAW: D32.1 (IO1), J9.1 (SPEED_SIG), R43.2, R44.1
SW: C11.2, L1.1, U2.3 (NC), U2.12 (SW)
SWCLK: J2.4 (SWCLK), U1.62 (SWCLK)
SWDIO: J2.2 (SWDIO), U1.64 (SWDIO)
SW_SENSE: R51.1, R53.1, U3.3 (SW)
TACH_IN: C56.1, D22.3 (CA), R77.2, R78.1, U1.57 (TACH_IN)
TACH_MID: R76.2, R77.1
TACH_RAW: J11.1 (TACH_SIG), R76.1, R79.2
TMR: C49.1, U3.9 (TMR)
TURN_LED_L_A: D24.3 (CA), D26.2 (A), R82.2
TURN_LED_R_A: D25.3 (CA), D27.2 (A), R83.2
U6_VLED: R6.2, U6.7 (VLED+)
U7_VLED: R7.2, U7.7 (VLED+)
U8_VLED: R8.2, U8.7 (VLED+)
U9_VLED: R9.2, U9.7 (VLED+)
UVLO_DIV: R53.2, R54.1, U3.4 (UVLO)
VCC_INT: C12.1, U2.5 (VCC)
VDDA: C8.1, L2.2, U1.8 (VDDA), U1.9 (VREFH)
VIN: F1.1, J1.1 (VIN)
VIN_FUSED: C62.1, D1.1, D34.1 (A1), F1.2, Q3.5 (D)
VIN_PROT: C1.1, C15.1, C46.1, C59.1, C60.1, C63.1, R19.1, R49.2, R92.1, U2.2 (VIN), U2.9 (EN), U2.10 (VIN), U5.10 (VBAT), U12.8 (VS)
VPULL: C64.1, J9.3 (SENSOR_12V), R43.1, R60.1, R63.1, R66.1, R69.1, R72.1, R75.1, R79.1, U12.7 (OUT)
VPULL_CL: R91.1, U12.4 (CL)
VPULL_DLY: R92.2, U12.5 (DELAY)
VPULL_EN: R90.1, U1.54 (VPULL_EN)
VPULL_IN: R90.2, U12.1 (IN)
VR_A: J12.1 (VR_A), R99.1
VR_B: J12.2 (VR_B), R100.1
VR_FP: C68.1, D35.3 (CA), R99.2, R101.1
VR_N: C69.1, D36.3 (CA), R100.2, R103.2, R104.1, U13.4 (IN-)
VR_P: R101.2, R102.1, U13.3 (IN+)
VR_SPEED_IN: R102.2, U1.56 (VR_SPEED_IN), U13.1 (OUT)

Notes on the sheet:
INPUT PROTECTION: LM74930-Q1 IDEAL DIODE + OV CLAMP + CURRENT LIMIT (review fix 2026-10-03)
AAOS, driving a larger round panel). CAN0 on THIS board now also carries gauge
CAN0: NXP TJA1043T TRANSCEIVER (PLAN STEP 2)
MCU CORE (NXP S32K144, 3.3V LOGIC) - FIXED PINS ONLY
SENSOR ADC FRONT END: FUEL / OIL / TEMP / BATTERY (PLAN STEP 5)
bare LED pair (not a logic pin), driven from +5V with a shared MOSFET switch.
drawn wires, with local labels only where pins are legitimately shared.
carriers to communicate.
VR SPEED INPUT: TWO-WIRE VARIABLE-RELUCTANCE SENSOR (4R70W, AOD-E, SOME T56), J12 + U13
PCB layout/routing/DRC/BOM are separate, not-yet-started next phases.
POWER INPUT, REVERSE-BATTERY + TRANSIENT PROTECTION
5V BUCK + 3.3V LDO
7. RE-SCOPED 2026-09-25: this board is the small-gauges half of Cluster's Android
U6-U9 (GC9A01) use Raystar's real RFA401280B-AYW-DNF1 pinout - backlight is a
5. Value fields tag automotive qualification: Q100 G1 = AEC-Q100 Grade 1 (ICs) -
pigtail and DTM06-3S plug; J7/J9/J10/J11 KK 254 headers with 22 AWG pigtails and
6. Harness (decided 2026-10-17, docs/harness.md): J1 Phoenix MKDS with a 20 AWG GXL
programmatically, not by eye. No generic placeholders anywhere.
curve (README.md), not a shared guess.
REVIEW 2026-10-17: CONNECTOR PROTECTION, SPI SERIES TERMINATION, EXTRA BULK, BACKLIGHT GATE PULL-DOWN
REVIEW 2026-11-03: SWITCHED SENDER EXCITATION + ADC BIAS (U11), SWITCHED 12 V PULL-UP / SENSOR RAIL (U12)
8. REV B (2026-09-30): gateway architecture. This board is the ONLY node on the car
Manual (same research thermo-pcb/manifold-pcb did for this part/package);
own embedded IO-signal-table attachment, cross-checked pin-by-pin for collisions
See protocol/ for the message set and the plan for the reasons.
CAN1 link (U10, J8). Added a Hall speed input (J9) and an ignition input (J1 pin 3).
2. Power stage (F1/Q1/U2/U3/U4 + supporting passives) reused VERBATIM from
REV C: INDICATOR LAMPS (6 x 12 V-ACTIVE) AND TACH INPUT
DTM06-6S / -3S / -08SA / -2S plugs; J8 an in-dash KK 254 cable to display/ J3.
sender readings - a real 3-node bus, per the user's own request for the two
3. U1 (S32K144) pin numbers are REAL - fixed pins verified against NXP's Reference
data pushed from that Android carrier, not just ecu-pcb traffic and local
REV B: HALL SPEED INPUT (AutoMeter-type 12 V pulse sender)
Automotive re-architecture - the center speedo (BT817AQ + ST7701S) moved to a
REV B: CAN1 PRIVATE LINK TO display/ (TCAN1044V-Q1)
peripheral pins (LPSPI2/FlexCAN0/4xADC/GPIO) verified against the same Manual's
manifold-pcb/thermo-pcb's own proven, real circuit - not re-derived here.
separate carrier, cluster-pcb/display/ (Verdin iMX95 + SN65DSI85-Q1, running
4. U5 (TJA1043T) reused verbatim from ecu-pcb's own real CAN transceiver circuit.
R16-R20 (sensor dividers) are each sized from the sender's own real resistance

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
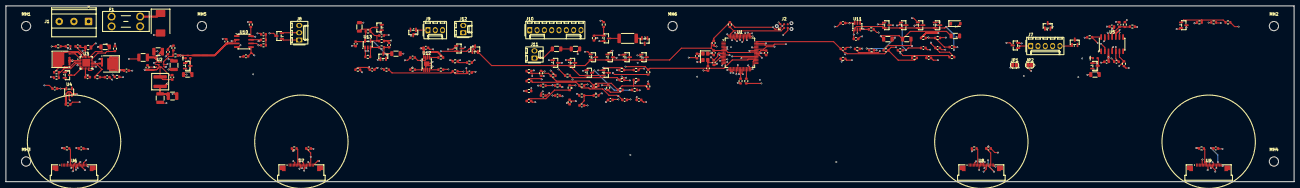
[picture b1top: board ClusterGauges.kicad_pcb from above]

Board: 6 copper layers, 447.1 x 61.0 mm, 202 parts (0 on the bottom side), 115 nets.

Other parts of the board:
MH1, MH2, MH3, MH4, MH5, MH6: MountingHole_3.2mm_M3
